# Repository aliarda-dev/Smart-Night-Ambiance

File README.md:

***Smart Ambient Lighting System (LDR-Controlled)***

LDR (fotorezistör) ile ortam ışığını ölçen, karanlıkta otomatik olarak LED'i açan basit bir akıllı aydınlatma prototipi.

***Donanım***

Arduino Uno
LDR (Fotorezistör)
1x LED
10kΩ Direnç (gerilim bölücü)
330Ω Direnç (LED koruma)

***Nasıl Çalışır?***

LDR ve 10kΩ direnç gerilim bölücü oluşturur
A0 pininden ADC ile 0-1023 arası değer okunur
Belirlenen threshold değerinin altına düşülürse LED yanar
Serial Monitor üzerinden anlık sensör değeri izlenebilir

***Teknik Notlar***

Gerilim bölücü prensibi ile analog sinyal dijitale çevrildi
Threshold değeri deneme-yanılma ile ayarlandı, ortama göre değişir

***Geliştirme Fikirleri***

Adaptive threshold (hareketli ortalama ile)
PWM ile ışık şiddetine orantılı parlaklık

***Not***

Projenin PCB tasarımı için pil güç kaynaklı gerekli dosyaları yüklendi.

🎥 Proje Demo Videosu

https://github.com/user-attachments/assets/69747c30-c749-4ff2-bb1d-25689b94c900

-📷 Proje PCB Medyası

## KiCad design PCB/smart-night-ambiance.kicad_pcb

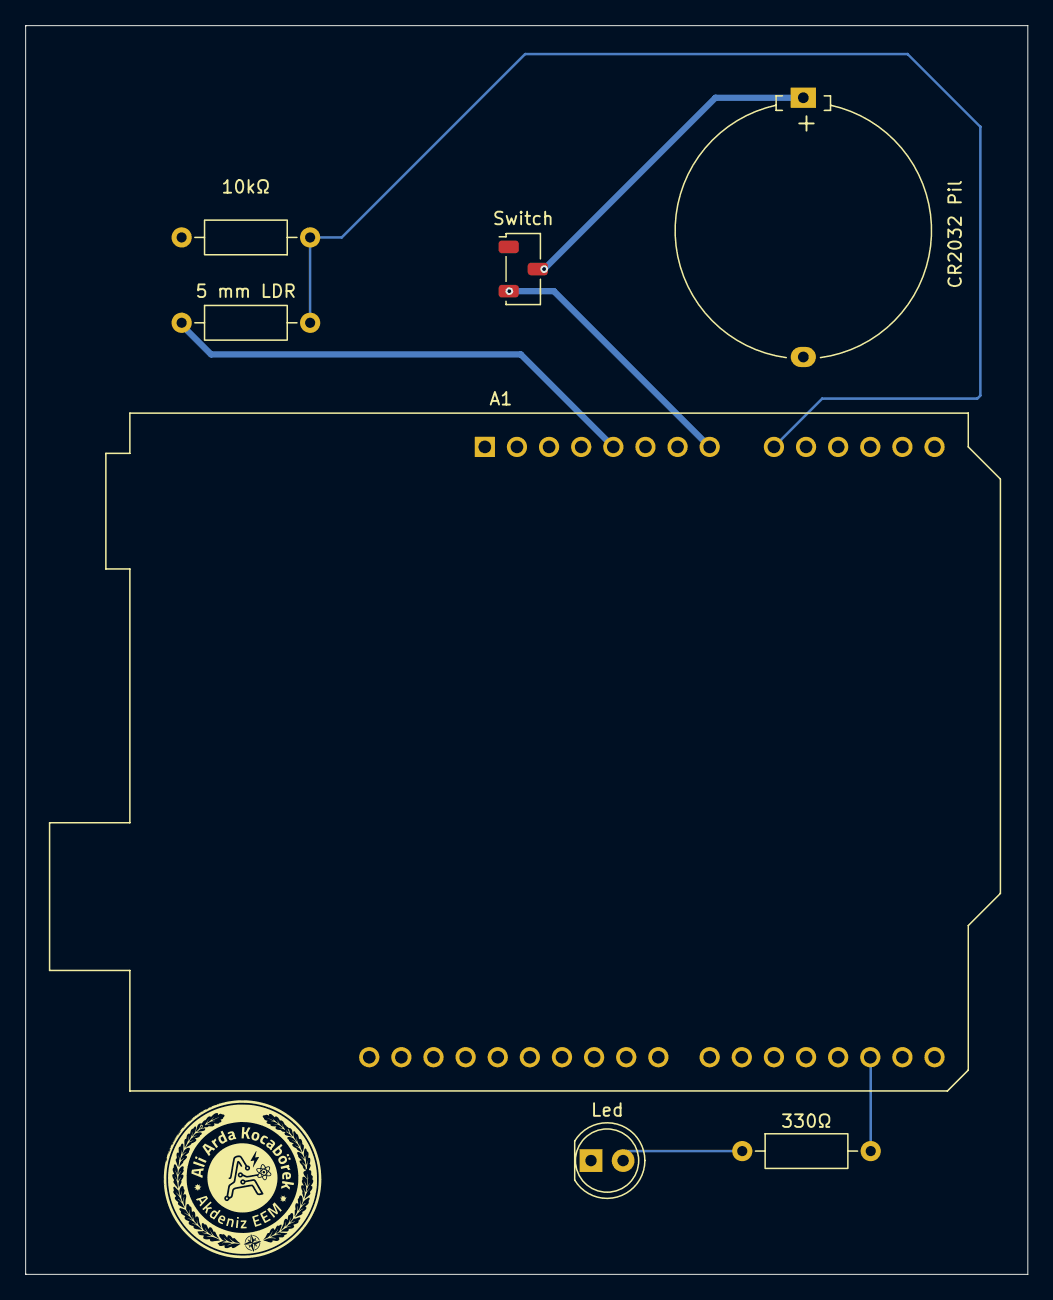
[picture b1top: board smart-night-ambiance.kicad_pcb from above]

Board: 2 copper layers, 79.2 x 98.8 mm, 7 parts (0 on the bottom side), 7 nets.

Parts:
5 mm LDR: R_Photo; R_Axial_DIN0207_L6.3mm_D2.5mm_P10.16mm_Horizontal
10kΩ: 10kR; R_Axial_DIN0207_L6.3mm_D2.5mm_P10.16mm_Horizontal
330Ω: 330R; R_Axial_DIN0207_L6.3mm_D2.5mm_P10.16mm_Horizontal
A1: Arduino_UNO_R3
CR2032 Pil: Battery_Cell; Battery_Panasonic_CR2032-HFN_Horizontal_CircularHoles
Led: LED; LED_D5.0mm
Switch: SW_Nidec_CAS-120A1; Nidec_Copal_CAS-120A

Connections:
2: 330Ω.2, A1.17 (D2)
5V: 5 mm LDR.1, A1.5 (+5V)
A0: 5 mm LDR.2, 10kΩ.1, A1.9 (A0)
GND: 10kΩ.2, A1.6 (GND), A1.7 (GND), A1.29 (GND), CR2032 Pil.2 (-), Led.1 (K)
unnamed: CR2032 Pil.1 (+), Switch.2 (B)
unnamed: 330Ω.1, Led.2 (A)
VIN: A1.8 (VIN), Switch.3 (A)

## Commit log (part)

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2026-02-13 About Smart Night Ambiance Project
2026-02-14 Added Media
2026-02-14 Arduino IDE Code for Smart Night Ambiance Project
2026-04-20 Arduino IDE Code for Smart Night Ambiance
